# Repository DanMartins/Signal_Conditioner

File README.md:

# Signal_Conditioner 

Hardware development for IoTControl to interface with analog signals for control systems on [PhD program at University of São Paulo](http://ppgee.poli.usp.br). Part of this work is open source and available here on [GitHub](https://github.com/DanMartins) and there is a channel on [YouTube][youtube] where you can find videos about IoTControl platform.

You may want to reach me on [LinkedIn][linkedin] or [ResearchGate](https://www.researchgate.net/profile/Danilo_Oliveira_Martins), publications are available on [ORCID][orcid] and [Lattes](http://lattes.cnpq.br/4247658321049641).

<!--
-->
[youtube]: https://www.youtube.com/channel/UCRJF9ALztqDIZ913XhoeNug
[linkedin]: https://www.linkedin.com/in/danilo-martins-phd
[orcid]: https://orcid.org/0000-0002-3035-7137

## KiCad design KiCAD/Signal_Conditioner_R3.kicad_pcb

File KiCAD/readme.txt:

KiCAD project folder, signal conditioner hardware.

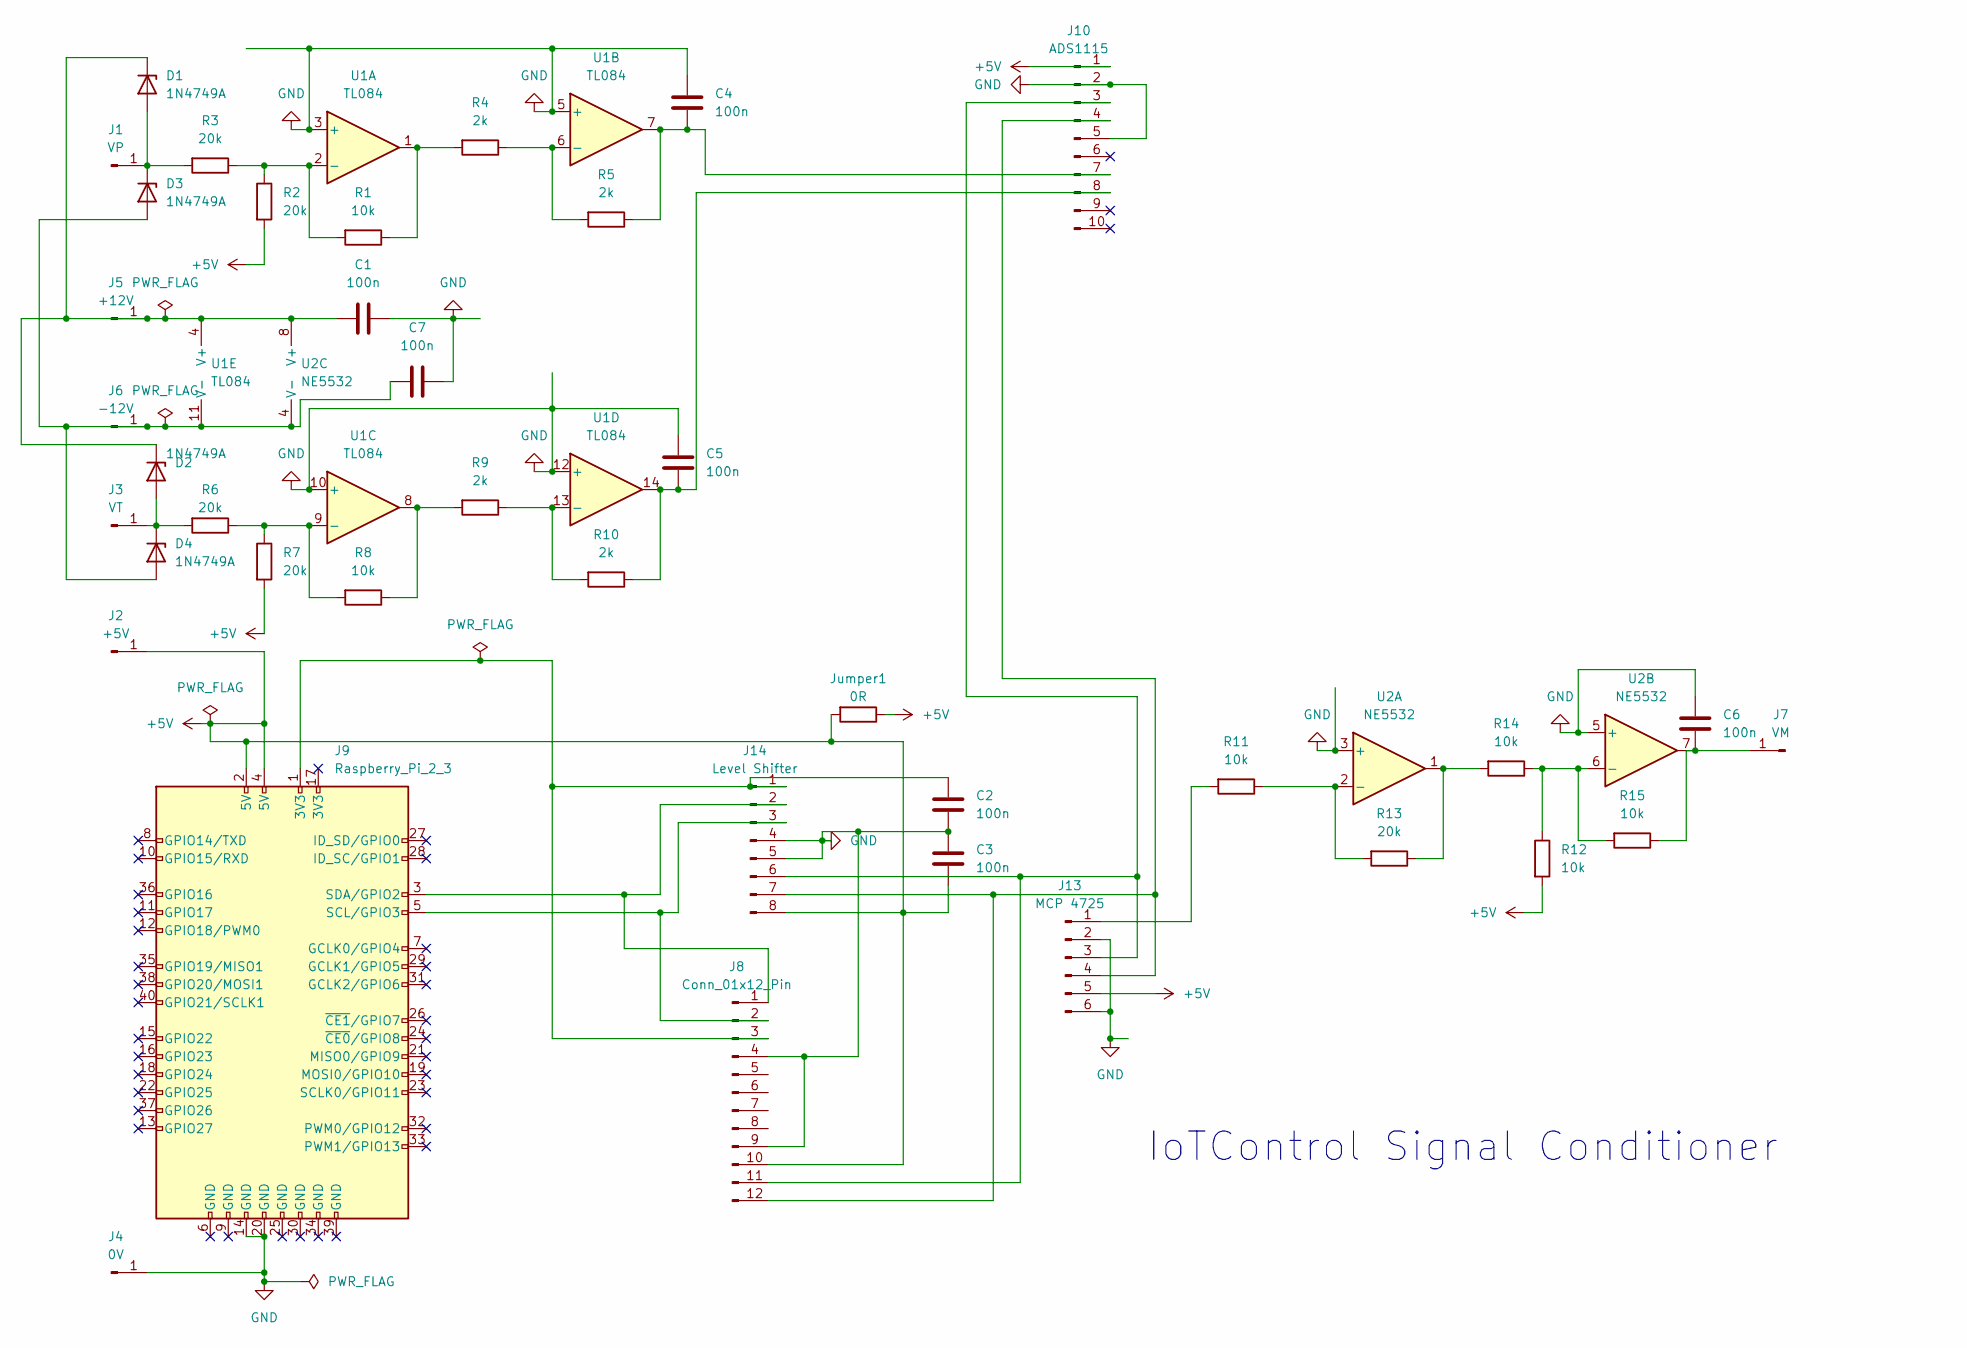
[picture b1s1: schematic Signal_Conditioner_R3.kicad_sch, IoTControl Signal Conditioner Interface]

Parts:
C1, C2, C3, C4, C5, C6, C7: 100n; C_Rect_L4.6mm_W2.0mm_P2.50mm_MKS02_FKP02
D1, D2, D3, D4: 1N4749A; D_DO-35_SOD27_P7.62mm_Horizontal
J1: VP; MountingHole_2.2mm_M2_Pad
J2: +5V; MountingHole_2.2mm_M2_Pad
J3: VT; MountingHole_2.2mm_M2_Pad
J4: 0V; MountingHole_2.2mm_M2_Pad
J5: +12V; MountingHole_2.2mm_M2_Pad
J6: -12V; MountingHole_2.2mm_M2_Pad
J7: VM; MountingHole_2.2mm_M2_Pad
J8: Conn_01x12_Pin; DIP-12_DAN.GPIO_Conn
J9: Raspberry_Pi_2_3; DIP-40_DAN_EXT-RaspGPIO
J10: ADS1115; PinSocket_1x10_P2.54mm_Vertical
J13: MCP 4725; PinHeader_1x06_P2.54mm_Vertical
J14: Level Shifter; DIP-8_DAN GPIO Connector
Jumper1: 0R; R_Axial_DIN0207_L6.3mm_D2.5mm_P10.16mm_Horizontal
R1, R8, R11, R12, R14, R15: 10k; R_Axial_DIN0207_L6.3mm_D2.5mm_P7.62mm_Horizontal
R2, R3, R6, R7, R13: 20k; R_Axial_DIN0207_L6.3mm_D2.5mm_P7.62mm_Horizontal
R4, R5, R9, R10: 2k; R_Axial_DIN0207_L6.3mm_D2.5mm_P7.62mm_Horizontal
U1: TL084; DIP-14_W7.62mm_Socket
U2: NE5532; DIP-8_W7.62mm_Socket

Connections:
+5V: C3.2, J2.1, J8.10, J9.2 (5V), J9.4 (5V), J10.1, J13.5, J14.8, Jumper1.1, Jumper1.2, R2.2, R7.2, R12.2
GND: C1.1, C2.2, C3.1, C4.1, C5.1, C6.1, C7.2, J4.1, J8.4, J8.9, J9.14 (GND), J9.20 (GND), J10.2, J10.5, J13.2, J13.6, J14.4, J14.5, U1.3 (+), U1.5 (+), U1.10 (+), U1.12 (+), U2.3 (+), U2.5 (+)
unnamed: D1.2 (A), D3.1 (K), J1.1, R3.2
unnamed: C1.2, D1.1 (K), D2.1 (K), J5.1, U1.4 (V+), U2.8 (V+)
unnamed: D2.2 (A), D4.1 (K), J3.1, R6.2
unnamed: C7.1, D3.2 (A), D4.2 (A), J6.1, U1.11 (V-), U2.4 (V-)
unnamed: C6.2, J7.1, R15.1, U2.7
unnamed: J8.11, J10.3, J13.3, J14.6
unnamed: J8.12, J10.4, J13.4, J14.7
unnamed: C4.2, J10.7, R5.1, U1.7
unnamed: C5.2, J10.8, R10.1, U1.14
unnamed: J13.1, R11.2
unnamed: C2.1, J8.3, J9.1 (3V3), J14.1
unnamed: J8.1, J9.3 (SDA/GPIO2), J14.2
unnamed: J8.2, J9.5 (SCL/GPIO3), J14.3
unnamed: R1.1, R4.2, U1.1
unnamed: R8.1, R9.2, U1.8
unnamed: R13.1, R14.2, U2.1
unnamed: R1.2, R2.1, R3.1, U1.2 (-)
unnamed: R4.1, R5.2, U1.6 (-)
unnamed: R6.1, R7.1, R8.2, U1.9 (-)
unnamed: R9.1, R10.2, U1.13 (-)
unnamed: R11.1, R13.2, U2.2 (-)
unnamed: R12.1, R14.1, R15.2, U2.6 (-)

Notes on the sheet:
IoTControl Signal Conditioner

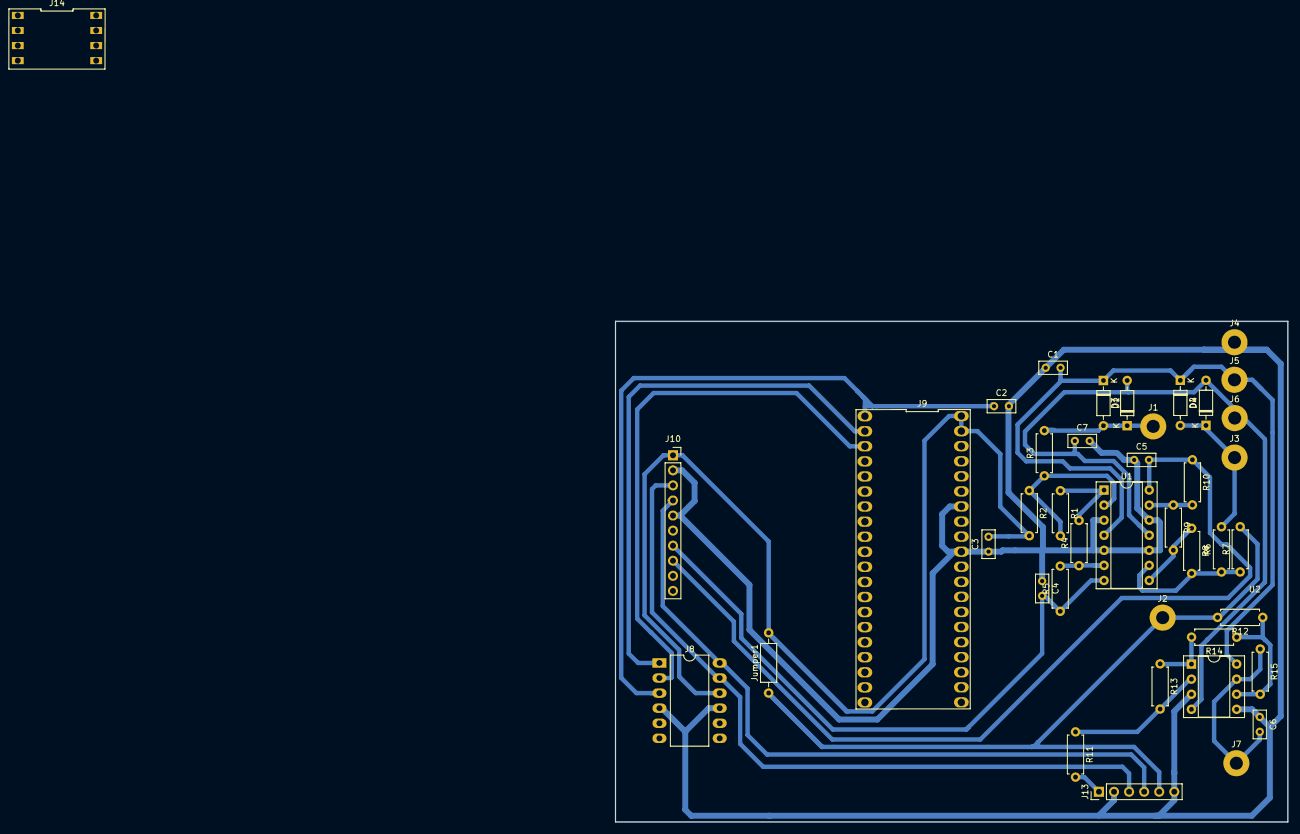
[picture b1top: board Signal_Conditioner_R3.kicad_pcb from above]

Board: 2 copper layers, 113.3 x 84.4 mm, 41 parts (0 on the bottom side), 24 nets.

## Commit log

2026-02-27 Update README to clarify hardware development focus
2026-02-27 Update README with additional links and image
2026-02-27 Revise CITATION.cff with new metadata and details
    Updated citation information and added abstract, keywords, and license details.
2026-02-27 Add DOI badge to README
    Added DOI badge for project citation.
2026-02-27 Fix header formatting in README.md
    Updated header formatting for consistency.
